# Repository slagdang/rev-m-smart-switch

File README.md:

# Smart switched outlet (2025) teardown

## History and product overview

A smart switched outlet is actually a device that plugs into a non-switched
outlet and has its own power outlet on it. The device is controllable remotely
over Wi-Fi and allows the device to be turned on and off.

This smart switched outlet is sold by Meross.
Meross describes it as a Matter smart plug.
It uses Matter over IPv6 over WiFi. It does not use Thread.
This is for US voltage and outlets. It was purchased in July 2025.
The device allows switching of the outlet and remote monitoring of
the switch state. It also allows continuous monitoring of the power
and energy usage by the attached switched device.

## Electrical background

In the US most appliances use 3-prong plugs with two parallel blade conductors
for the power conduction and a round pin for the protective ground.
The standard outlet for 120V at up to 15A (60Hz) is a NEMA 5-15R.
The plug that goes into it is a NEMA 5-15P.
The power is provided with one blade conductor that is at 120VAC RMS potential
compared to ground (called live, line or hot) and one blade conductor that
is at zero potential compared to ground (called neutral or return).

Protective ground should never be interrupted so that the device is grounded even
when off.
To turn a device off it is only necessary to interrupt the power circuit at any
point. This will cease current flow.
However it is safer to do this by interrupting the live conductor. This means all
circuitry in attached appliance will be at 0V potential as both conductors
still connected are at 0V potential.
To ensure the live is switched requires a polarized plug. In the US this is
done on ungrounded plugs with two different sized blades, one too large to fit
in the live slot. Grounded plugs with the round pin are inherently oriented
and do not require two different-sized blades.

## How it works

This device directly connects ground from the device socket to the wall plug
at all times. It also connects neutral continuously but places a current
sensing resistor in the path of the neutral connection.
It accomplishes its switching by interrupting the live line using a relay.

The relay is controlled using a single bit from a controller board that drives
a GPO line high or low. The main board also has an LED to indicate status
which is controlled by two GPO lines. It has a power and energy monitoring
chip which is read out by the controller board over a 4800bps 5V logic-level
RS-232 serial line.

## Circuit analysis

[view schematic as a PDF here.](smart-outlet-m-reverse.pdf)

The device contains a transformerless switching power supply to generate a
neutral-referenced 5V supply used to actuate the relay.
It has a 3.3V low dropout linear regulator to further reduce this for
use by the measurement chip and the microcontroller.
It contains a controller sub-module which has a Realtek Bluetooth radio
and microcontroller (RTL8720CM) which utilizes the 3.3V supply.
It measures current as a voltage differential across a 1mΩ sense resistor in
the neutral path from the device to the wall supply to measure instantaneous
current draw of the attached device.
It has a resistor chain from the live side into a voltage divider which is
then measured to determine the line voltage so power can be calculated.
It uses a 277V/16A-rated relay on the live side to turn the connected device
on and off.

The board has a bit over 1mm of creepage between RECT_AC and NEUTRAL_SRC.
It has the same clearance between the unswitched live and switched live.
For these conductors it is improved by using a 1mm slot.
The protective ground pin is not connected to anything inside except the
output receptacle.
The controller uses a GPO to turn the relay on and off through an NPN transistor.
It uses two GPOs to directly turn the LED red, green or off.
The controller uses a negative temperature coefficient thermistor to measure
the internal temperature of the device through an analog input,
presumably for protection.
The controller reads power draw parameters from a measurement chip over a
serial link.
The power input is fused for the controlling circuitry with a self-resetting
polyfuse and uses a metal-oxide varistor to withstand surges.
Power through the unit to the attached device is not protected with a fuse
or similar.

### Main schematic page

The function button (SW1) is read on a GPI to the controller board.
The button has an external pull up resistor (R23) so the GPI reads
high when the button is not pressed and low while it is pressed.

NTC1 is a temperature-sensitive resistor. It is read by being placed in a
resistive divider with R8. The node between them will change in voltage as
NTC1’s value changes. This voltage is read as an analog value through R7.
R7 will limit the current into the controller. As the analog input is
high impedance R7 does not form another voltage divider and so does not alter
the voltage read to a significant amount. The NTC1 cannot fully be
identified but likely has a B25/50 value of 4250K as this is the type
commonly used to measure human-scale ambient temperatures.

LED1 is referenced to 3.3V and so the emitters are turned on by driving
LED_RED or LED_GREEN low.

C13 and C14 are smoothing capacitors to smooth the voltage provided to the
controller circuitry.

### Power control page

Several functions are provided on this page. The simplest is to connect input
ground directly to the ground on the power outlet side.

The second is to
connect input neutral to the neutral on the power outlet side. Neutral
passes through a 1mΩ resistor, R10. This allows current
to be measured by measuring the voltage drop (differential voltage) across
R10. Differential voltage is measured using Kelvin (4-wire) sensing through
the nets NEUTRAL_SRC_SENSE and NEUTRAL_LOAD_SENSE. The voltage is measured
on the inside edge of each end endcap of the resistor using a parallel
path to the current path and the difference between the two will be 1mV
for each 1A of current drawn by the switched device.

The third function is to supply AC power to the power supply circuit so it
can create 5V DC power from the AC power. The line voltage is divided by a
resistive divider comprising R25 and VR1. Despite the differing reference
designators both R25 and VR1 are variable resistance devices. R25 is a PTC
(positive temperature coefficient) polyfuse. VR1 is an NTC (negative
temperature coefficient) metal oxide varistor (MOV). When
connected to the wall
R25 will have a low resistance (20Ω or so) and NTC1 will have a very high
resistance. So FUSED_AC will be the same as the line voltage. R25 will limit
inrush current. If the control circuity draws too much current on FUSED_AC
the current through R25 will cause R25 to increase its resistance greatly
("blow"). The polyfuse will reset after a period of time and things
will start again. This will
repeat until the fault is cleared or the polyfuse fails completely and
the unit ceases to operate. If there is a high voltage surge from the wall
source then VR1 will begin to conduct (around 775V) and this will change
the voltage divider so FUSED_AC is reduced in voltage. It also will
increase current draw through R25 and so likely will trigger the polyfuse
also.

The final function is to switch the output live power on and off
using a relay. Relay K1 connects the output live to the wall source when
energized. K1 is energized by the controller applying a positive
logic-level voltage on POWER_EN. Once the base (pin 1) of Q1 is 0.6V
or more positive than the emitter (pin 2) then current flows into
the collector (pin 3) and out the emitter. This happens when POWER_EN
is driven high by the controller. This induces a current through R22
and the base. The current will be at least 3mA. This will cause Q1 to
attempt to drive at least 117mA through the collector through the coil
of K1. This is more
than enough to energize K1 fully. D4 serves to snub the voltage the
inductor (coil) in K1 produces momentarily when Q1 is switched off.
C17 serves to reduce the draw on +5V when the coil is first switched
on by producing a low ESR charge store.

### Power supplies page

The top half of this is a sophisticated neutral-referenced transformerless
switch-mode power supply (SMPS). The sophistication is mostly contained
within U1 and will not be fully explained here.

The short version is that U1 takes unregulated energy in and outputs
a reduced regulated voltage. It is capable of converting excess
voltage into increased current similar to how a transformer does
and the power (Watts) in is similar to the power out, just the
available voltage at the output is lower than the input and the
available current is increased inversely. It does this by rapidly
switching its output on and off to send energy into an inductor.
This inductor stores the energy in its magnetic field. It is drawn
off by the devices being supplied. It adjusts its switching duty
cycle so as to send the right amount of energy into the inductor
to match the energy being drawn out of the inductor and thus
keep the inductor voltage relatively constant. The inductor’s
resistance to current change and its ability to store energy in
its magnetic field are critical in making this happen.

Fused AC power at about 120V RMS comes in on FUSED_AC. D2 performs a positive
half-wave rectification on the AC. D5 applies a redundant half-wave
rectification. D5 is present only because diodes have some tendency to
become short circuits when failing. This would put AC voltage into the
circuit and produce a small conflagration within the device. By having two
diodes both D2 and D5 have to fail short to produce this result. This
should reduce the incidence of these small fires to the square of the
incidence rate with a single diode. So if this failure rate would be
one in one thousand over the life of the product then with two
consecutive diodes the failure rate would drop to one in a million
instead.

U1 and L2 work in tandem to drive the right-hand side of L2 to the
regulated voltage. This puts 5V across C7. R9 provides a minimum
current draw at the output to make the result of regulation through
switching more accurate.
U1 is rated for up to 300mA output current.

The bottom half of this page is a low-dropout linear regulator. A
linear regulator works by "burning off" any excess voltage at
the input so that the output voltage is regulated to the desired
value. This is usually done internally with a load resistor,
a current shunt and an op-amp.
U3 provides this regulation functionality on its own
and is fixed at 3.3V target output voltage. C10 and C11 provide
output smoothing. C9 provides input smoothing and
increases ripple rejection.

### Current measurement page

U3 is a complete current, voltage and power measurement solution.
It provides instantaneous voltage, current and power measurements
over a 4800bps 5V logic-level RS-232 serial link repeatedly every
54.912ms. These measurements can be accumulated over time to
calculate total energy used. The resistive divider created by
R12 and R13 reduce the serial output signal to 3.3V as the
controller uses 3.3V I/O. C15 provides supply voltage smoothing to
U3.

U3 measures the input voltage on pin 4 (V2P). Pin 4 cannot be
outside the range ±2V relative to GND. To overcome this the
resistive divider created by R14, R15, R16, R17 and R18 reduces
the input voltage to 0.0532% of the input voltage. This puts the
voltage in the range of ±100mV. Using multiple resistors is common
because of the high value needed and the high voltage at the
top of the divider. With 4 resistors on top of the ladder
each only drops up to 40V and so operates within the voltage
rating of an 0805 resistor instead of having to use a
more expensive large
format resistor. C16 smoothes the voltage and also
resists droop of the voltage when the sample and hold capacitor
on pin 4 captures the signal.

U3 measures the input current on pins 2 and 3 (V1P, V1N).
NEUTRAL_LOAD_SENSE and NEUTRAL_SRC_SENSE are connected to the
current sense resistor using the inner edges of the pads so
as to create a parallel path for voltage sensing (4-wire sensing).
R20, R24, C18 and C19 create low pass filters to reduce
unrepresentative readings for loads with spiky current draws.
Pins 2 and 3 are both on the neutral line which is no more than
1mΩ from GND and so should not
produce voltages which differ more than ±100mV from GND.

## Meta-analysis

Any criticisms here are constructive and do not necessarily indicate a serious
flaw in the product.

The power supply chip employed suggests using a full-bridge rectifier for its AC input.
However this design uses half-wave. It does however put two diodes in series so that
a single diode failing short does not produce a short. This is probably a reasonable
design choice.

The power supply chip regulates voltage referenced to system ground but is not
connected to system ground. Regulation is surely still acceptable but likely
less precise than could be achieved with a direct connection to the ground
reference.

The device contains no X-class capacitor at all. One is suggested for the power
supply chip but it is omitted. With no non-resetting fuse inside this may be the
right choice. It does seem to go against the company claims of "protection against
short-circuits" somewhat. Even if this has some software in the controller to
turn off on a measured overcurrent or over-temperature this device is relying on
wall circuit protection for true overcurrent protection.

While the device has internal temperature monitoring of a sort due to NTC1
it has no failsafe method of using that to prevent overheat. If the failure
which produces the overheat is not in the controller itself then the controller
will presumably use the temperature readings to shut down the attached device.
If the control circuity itself fails it will hopefully be shut down by the polyfuse
due to overcurrent.

The wireless interface chip is rated by the manufacturer at 500mA max current
draw. It is powered by a 3.3V LDO which is in a package too small to be rated
at 500mA. It surely is rated at 300mA or less. Despite this the LDO has 20µF of
capacitance on the outputvside. This normally would be for a 2A regulator.
In this case it seems that these capacitors are sized to try to make enough
instantaneous current available to overcome
the underrating of the LDO for short periods of high draw.
This seems to work fine but no measurements were made.

Measurements in U3 may be scaled up or down by choices of different
current sense resistors and voltage dividers. This must be
compensated for in software on the controller or on device software
that receives the readings over the network as U3 does not receive
commands and so cannot be instructed to rescale its calculations.

The small slit around the single button is not gasketed unlike another smart switched
outlet I purchased. This would mean liquids could ingress. It is nearest a low voltage
portion of the board and of course the button. The device also has the
receptacle on the front and those are not sealed so water could ingress there also
as it could on any similar device.

There are small quirks about the board layout. Unnecessary vias, etc. It uses a lot
of small floods in places. None of these issues are of importance.

### teardown images

### Device identification

The device is approximately 70mm wide by 40mm high by 40mm deep.
It has a NEMA 5-15P on the back to plug into a US outlet. It has
a NEMA 5-15R on the front for plugging in the device you wish to switch.
It is rated for 15 amps in and out and "120V" (presumably RMS nominal).

On the back it is identified as:

Smart WiFi Plug Mini

Model: MSS315

It lists as containing FCC ID 2AMUU-MWA05 and IC 24963-MWA06

## Design tools

This is a KiCAD 9.X project. KiCAD is a free electronic design tool
[available at kicad.org](https://kicad.org/).

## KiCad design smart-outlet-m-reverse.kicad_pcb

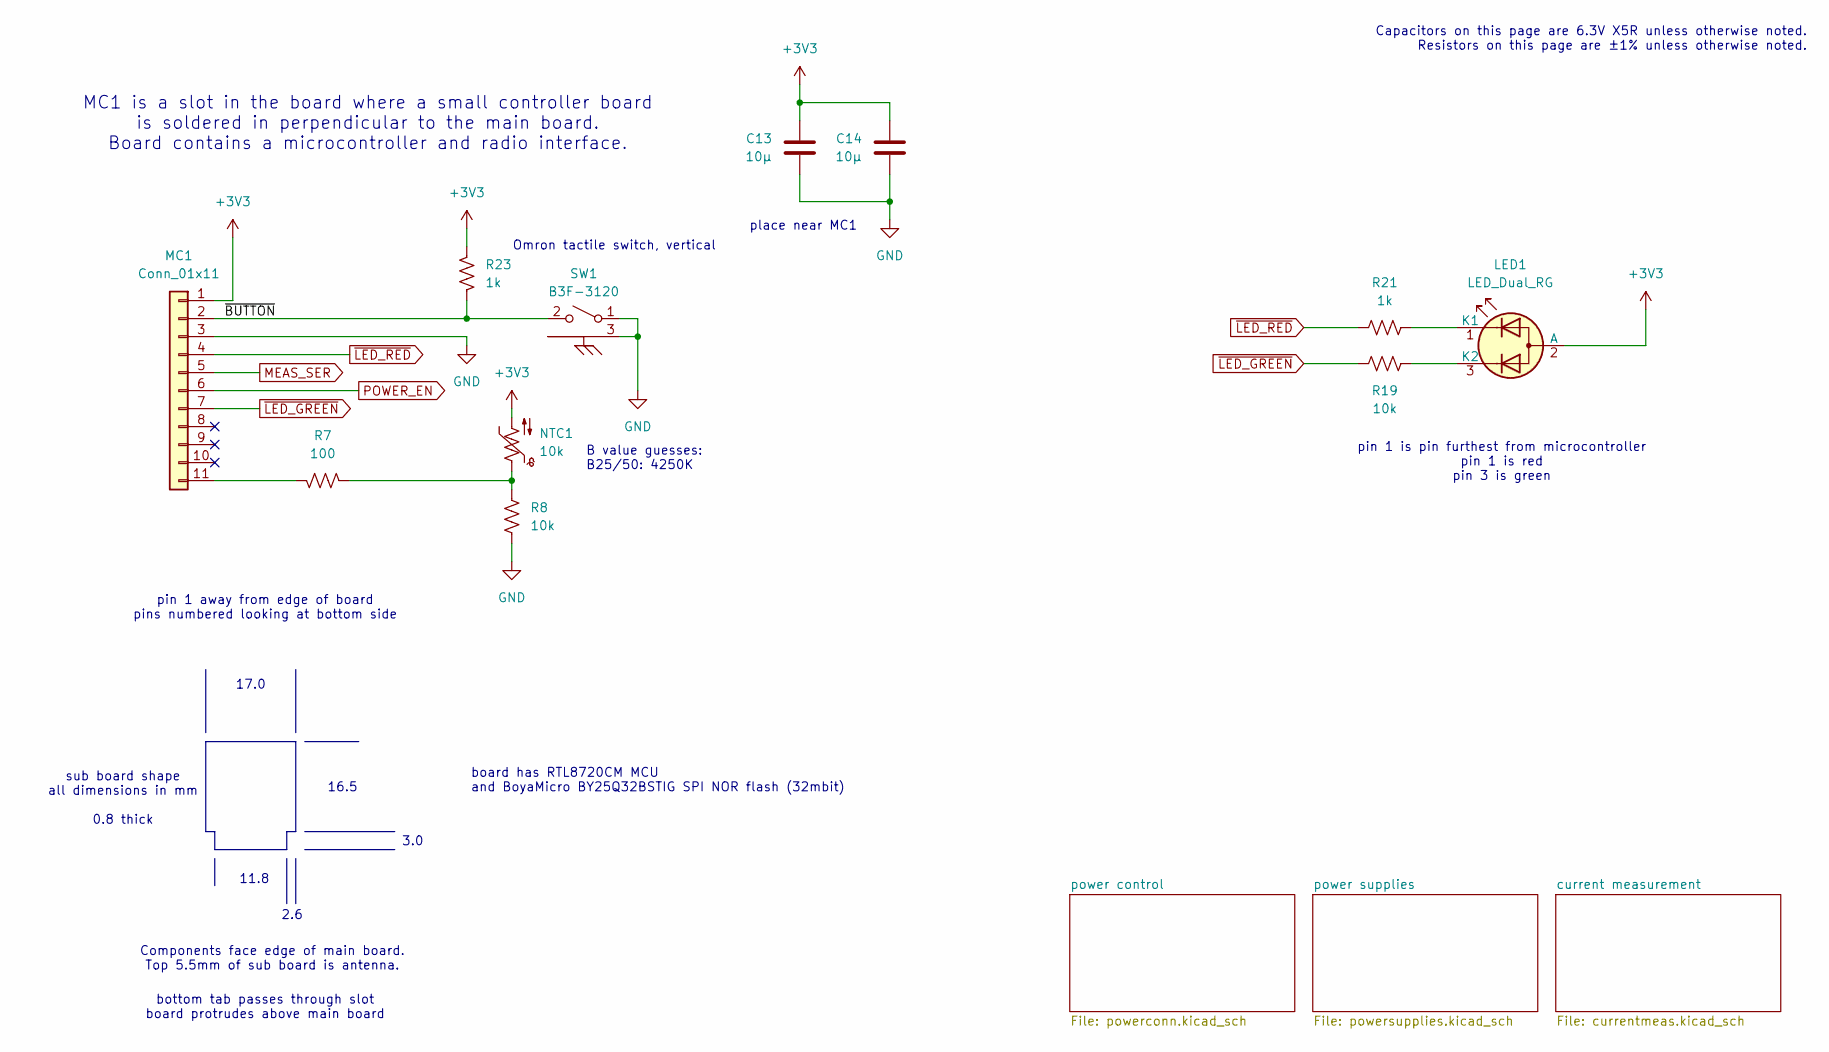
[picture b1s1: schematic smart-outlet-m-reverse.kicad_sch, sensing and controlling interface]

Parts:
C13, C14: 10µ; C_0402_1005Metric
LED1: LED_Dual_RG; LED_D3.0mm-3_Horiz
MC1: Conn_01x11; BoardToBoardInterface_11xP1.00mm
NTC1: 10k; R_0402_1005Metric
R7: 100; R_0402_1005Metric
R8, R19: 10k; R_0402_1005Metric
R21, R23: 1k; R_0402_1005Metric
SW1: B3F-3120; SW_SPST_Omron_B3F-315x_Angled

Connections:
+3V3: C13.2, C14.2, LED1.2 (A), MC1.1, NTC1.2, R23.1; also elsewhere on the board
/~BUTTON: MC1.2, R23.2, SW1.2 (B)
MEAS_SER: MC1.5; also elsewhere on the board
NEUTRAL_SRC: C13.1, C14.1, MC1.3, R8.1, SW1.1 (A), SW1.3; also elsewhere on the board
unnamed: LED1.1 (K1), R21.2
unnamed: LED1.3 (K2), R19.2
unnamed: MC1.11, R7.1
unnamed: NTC1.1, R7.2, R8.2
POWER_EN: MC1.6; also elsewhere on the board
~LED_GREEN: MC1.7, R19.1
~LED_RED: MC1.4, R21.1

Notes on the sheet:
2.6
bottom tab passes through slot board protrudes above main board
11.8
Omron tactile switch, vertical
3.0
16.5
place near MC1
B value guesses: B25/50: 4250K
sub board shape all dimensions in mm 0.8 thick
pin 1 away from edge of board pins numbered looking at bottom side
17.0
pin 1 is pin furthest from microcontroller pin 1 is red pin 3 is green
MC1 is a slot in the board where a small controller board is soldered in perpendicular to the main board. Board contains a microcontroller and radio interface.
board has RTL8720CM MCU and BoyaMicro BY25Q32BSTIG SPI NOR flash (32mbit)
Capacitors on this page are 6.3V X5R unless otherwise noted. Resistors on this page are ±1% unless otherwise noted.
Components face edge of main board. Top 5.5mm of sub board is antenna.

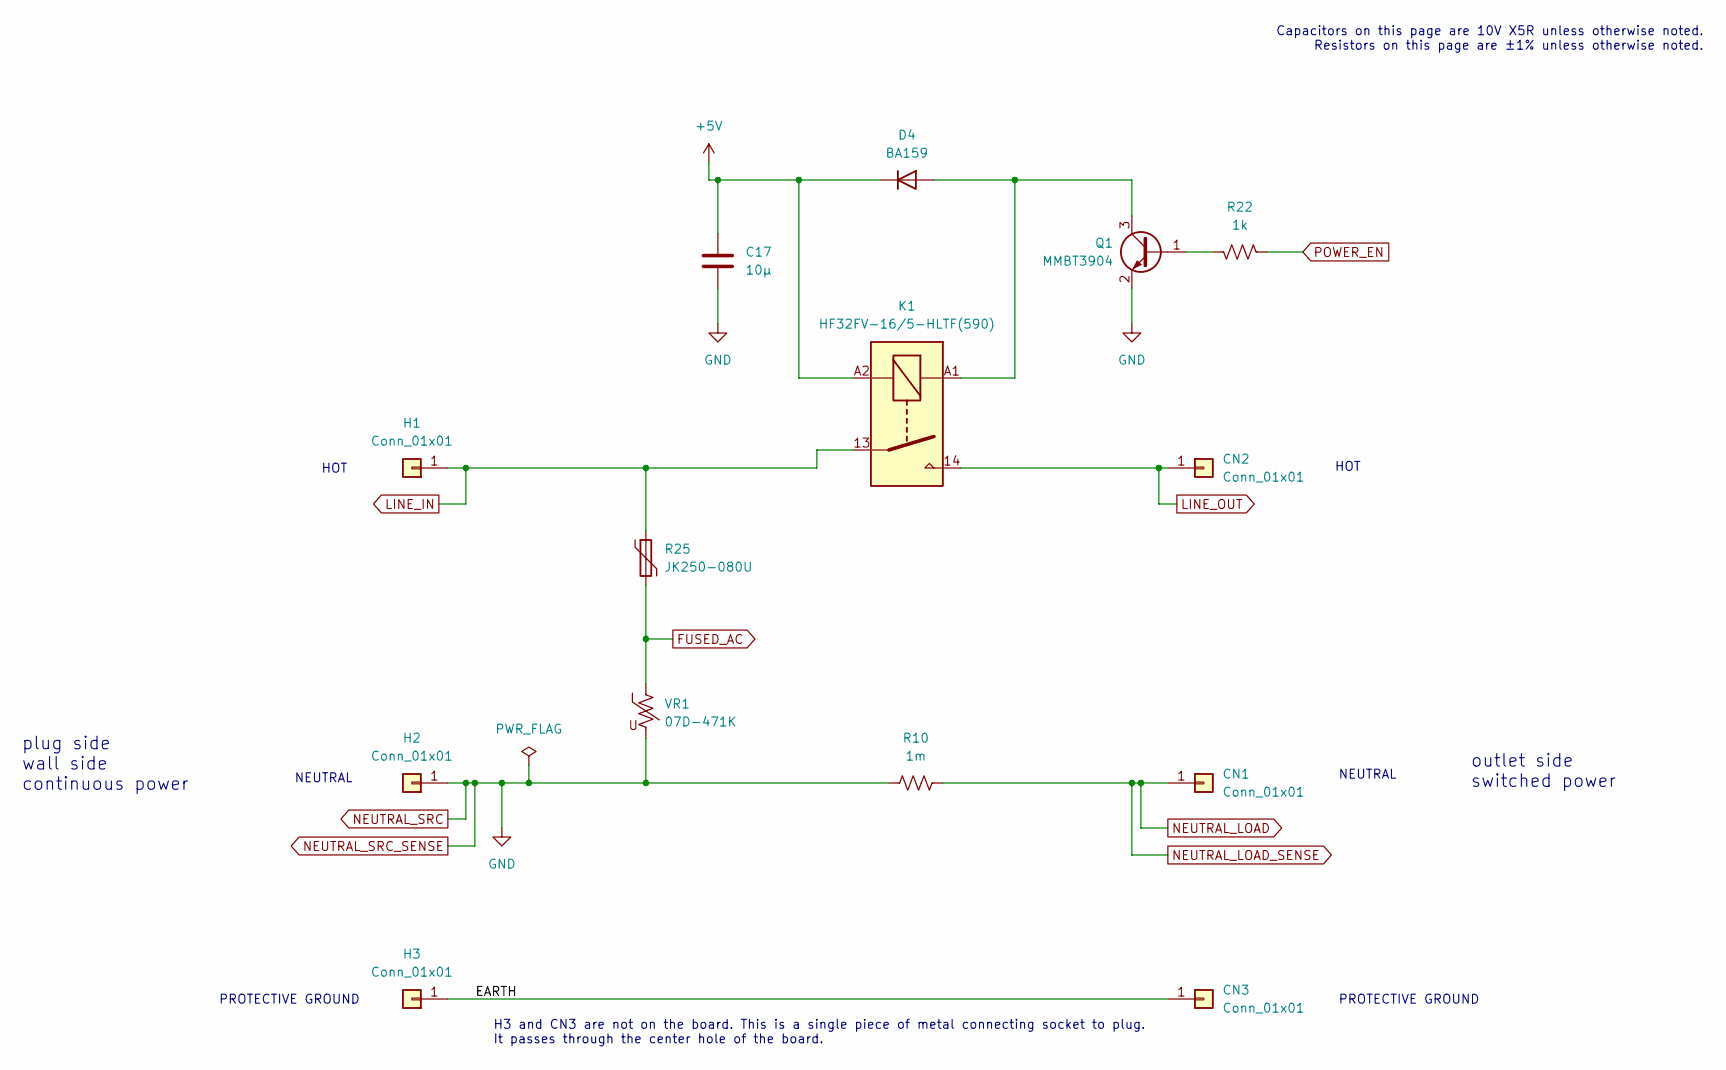
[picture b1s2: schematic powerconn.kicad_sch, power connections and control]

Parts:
C17: 10µ; C_0603_1608Metric
CN1, CN2: Conn_01x01; NEMA5R_blade
CN3: Conn_01x01; PinHeader_1x01_P2.54mm_Vertical
D4: BA159; D_SOD-123F
H1, H2: Conn_01x01; NEMA5P_post
H3: Conn_01x01; PinHeader_1x01_P2.54mm_Vertical
K1: HF32FV-16/5-HLTF(590); HF_Relay_subminature_A_THT_18.4x10.2mm
Q1: MMBT3904; SOT-23
R10: 1m; R_2512_6332Metric
R22: 1k; R_0402_1005Metric
R25: JK250-080U; Fuse_Littelfuse_395Series
VR1: 07D-471K; RV_Disc_D9mm_W6.1mm_P5mm

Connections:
+5V: C17.1, D4.1 (K), K1.A2; also elsewhere on the board
FUSED_AC: R25.2, VR1.1; also elsewhere on the board
LINE_IN: H1.1, K1.13, R25.1
LINE_OUT: CN2.1, K1.14
NEUTRAL_LOAD: CN1.1, R10.2; also elsewhere on the board
NEUTRAL_SRC: C17.2, H2.1, Q1.2 (E), R10.1, VR1.2; also elsewhere on the board
unnamed: CN3.1, H3.1
unnamed: D4.2 (A), K1.A1, Q1.3 (C)
unnamed: Q1.1 (B), R22.2
POWER_EN: R22.1; also elsewhere on the board

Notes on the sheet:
Capacitors on this page are 10V X5R unless otherwise noted. Resistors on this page are ±1% unless otherwise noted.
PROTECTIVE GROUND
HOT
plug side wall side continuous power
outlet side switched power
NEUTRAL
H3 and CN3 are not on the board. This is a single piece of metal connecting socket to plug. It passes through the center hole of the board.

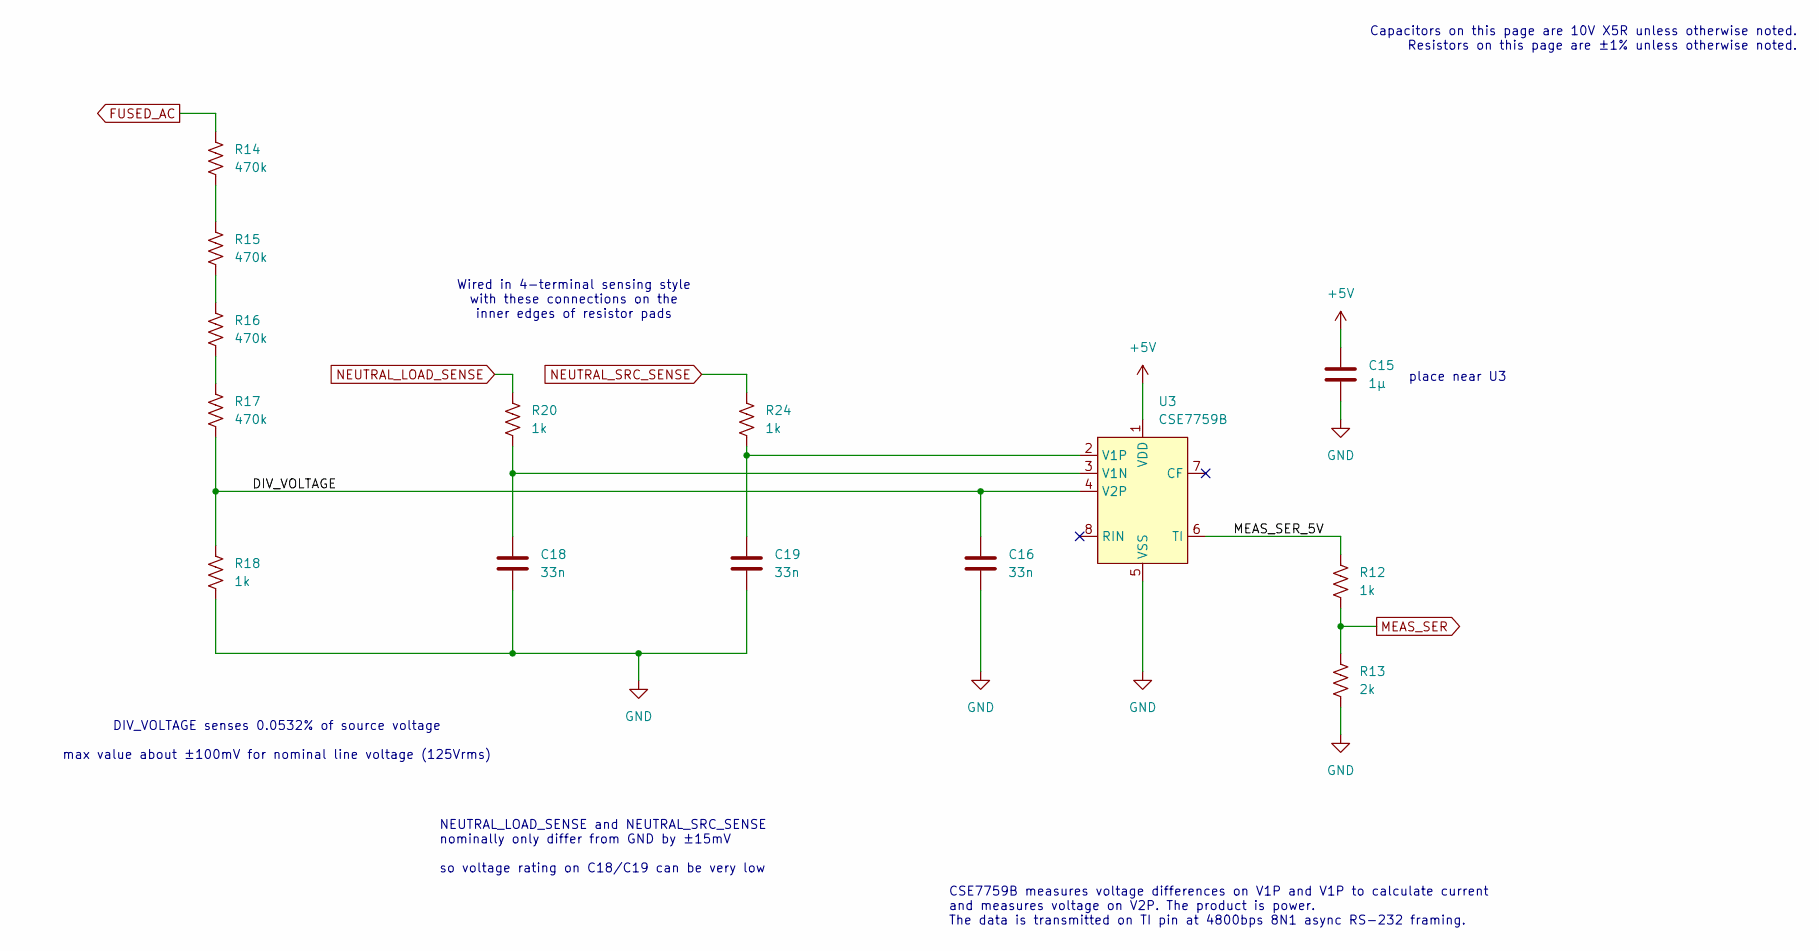
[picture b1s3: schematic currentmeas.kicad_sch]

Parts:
C15: 1µ; C_0402_1005Metric
C16, C18, C19: 33n; C_0402_1005Metric
R12, R18, R20, R24: 1k; R_0402_1005Metric
R13: 2k; R_0402_1005Metric
R14, R15, R16, R17: 470k; R_0805_2012Metric
U3: CSE7759B; SO-8_3.9x4.9mm_P1.27mm

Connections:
+5V: C15.1, U3.1 (VDD); also elsewhere on the board
/current measurement/DIV_VOLTAGE: C16.1, R17.1, R18.2, U3.4 (V2P)
/current measurement/MEAS_SER_5V: R12.1, U3.6 (TI)
FUSED_AC: R14.2; also elsewhere on the board
MEAS_SER: R12.2, R13.1; also elsewhere on the board
NEUTRAL_LOAD: R20.1; also elsewhere on the board
NEUTRAL_SRC: C15.2, C16.2, C18.2, C19.2, R13.2, R18.1, R24.1, U3.5 (VSS); also elsewhere on the board
unnamed: R14.1, R15.2
unnamed: R15.1, R16.2
unnamed: R16.1, R17.2
unnamed: C18.1, R20.2, U3.3 (V1N)
unnamed: C19.1, R24.2, U3.2 (V1P)

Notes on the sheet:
NEUTRAL_LOAD_SENSE and NEUTRAL_SRC_SENSE nominally only differ from GND by ±15mV so voltage rating on C18/C19 can be very low
Capacitors on this page are 10V X5R unless otherwise noted. Resistors on this page are ±1% unless otherwise noted.
place near U3
Wired in 4-terminal sensing style with these connections on the inner edges of resistor pads
CSE7759B measures voltage differences on V1P and V1P to calculate current and measures voltage on V2P. The product is power. The data is transmitted on TI pin at 4800bps 8N1 async RS-232 framing.
DIV_VOLTAGE senses 0.0532% of source voltage max value about ±100mV for nominal line voltage (125Vrms)

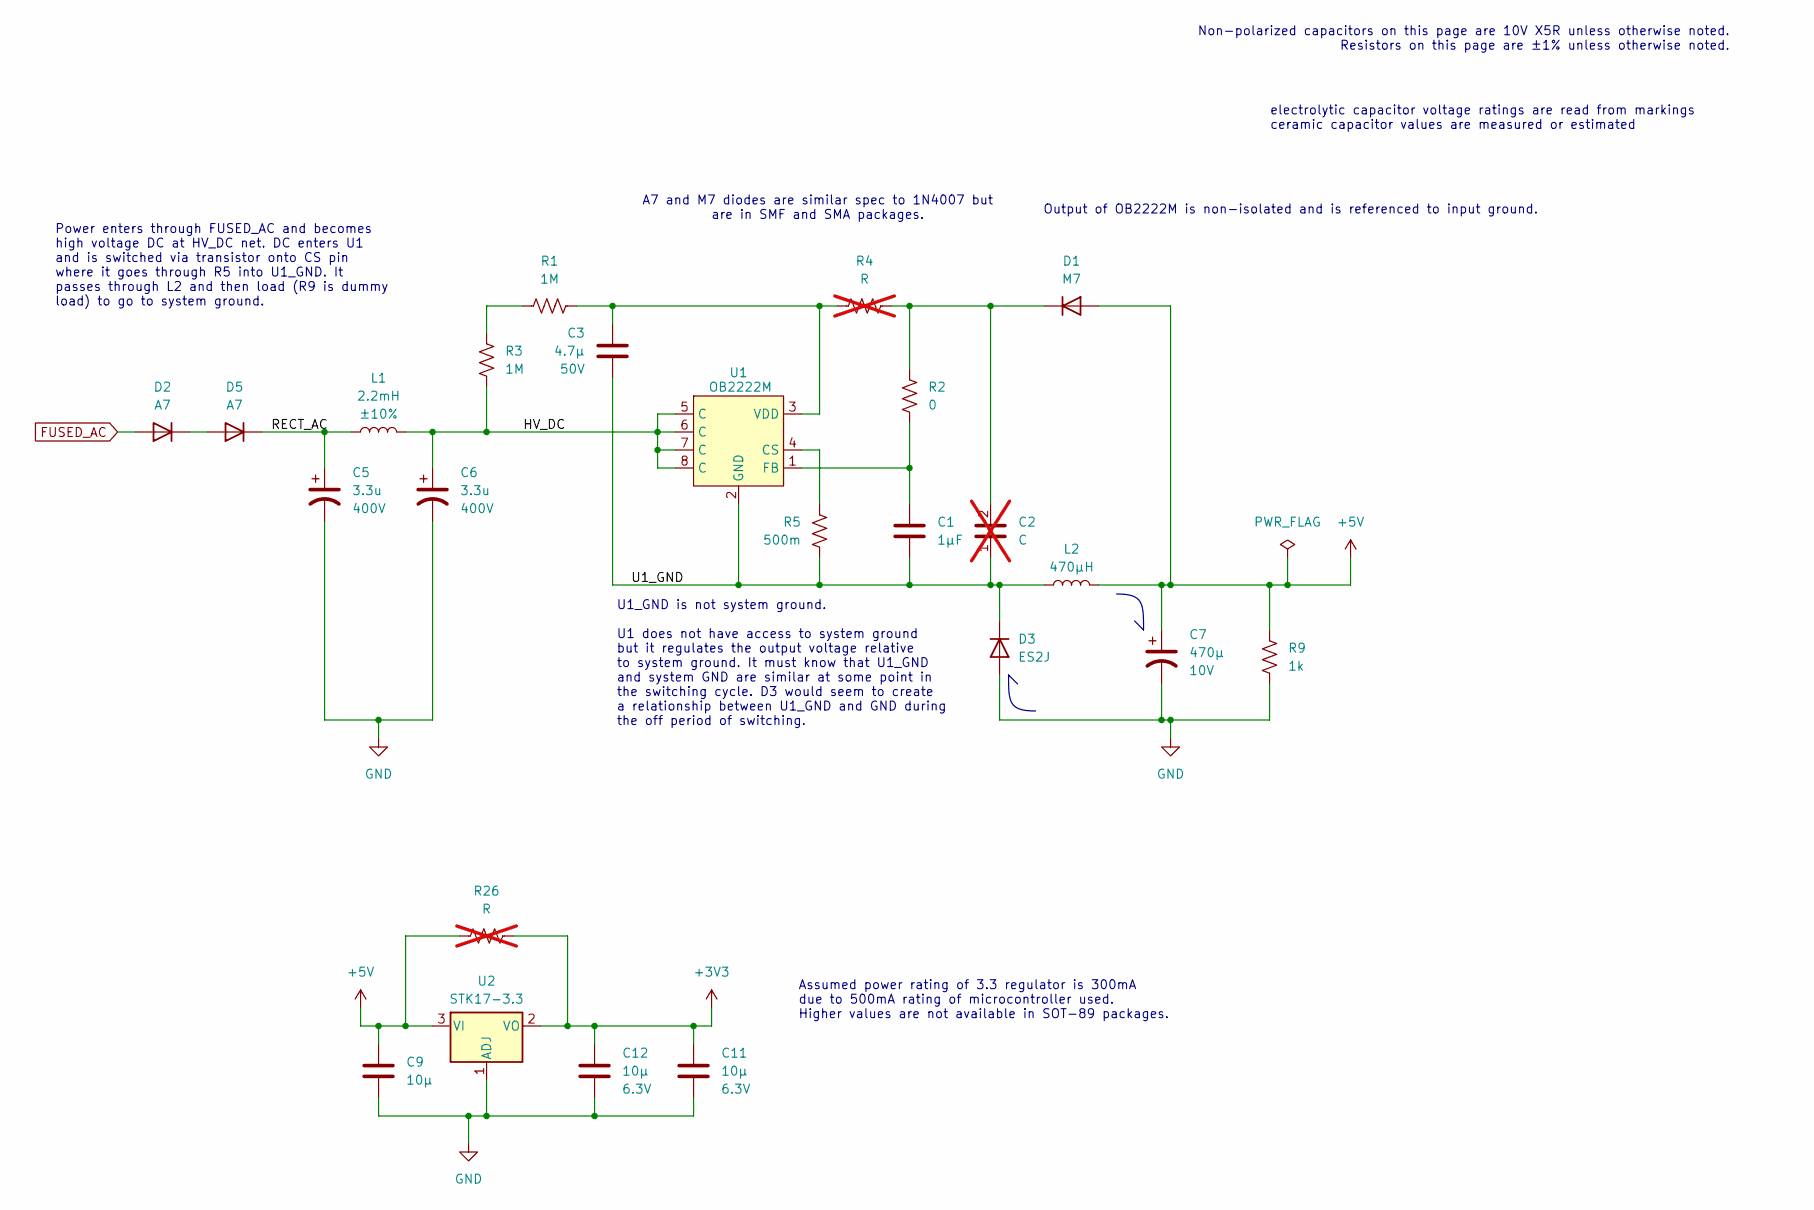
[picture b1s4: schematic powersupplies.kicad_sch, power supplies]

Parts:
C1: 1µF; C_0603_1608Metric
C2: C; C_0603_1608Metric; not fitted
C3: 4.7µ; C_0805_2012Metric; Voltage 50V
C5, C6: 3.3u; CP_Radial_D6.3mm_P2.50mm; Voltage 400V
C7: 470µ; CP_Radial_D6.3mm_P2.50mm; Voltage 10V
C9: 10µ; C_0603_1608Metric
C11, C12: 10µ; C_0402_1005Metric; Voltage 6.3V
D1: M7; D_SMA
D2, D5: A7; D_SOD-123F
D3: ES2J; D_SMA
L1: 2.2mH; L_Axial_L9.5mm_D4.0mm_P3.81mm_Vertical; Tolerance ±10%
L2: 470µH; L_Radial_D8.7mm_P5.00mm_Fastron_07HCP
R1, R3: 1M; R_0805_2012Metric
R2: 0; R_0603_1608Metric
R4, R26: R; R_0603_1608Metric; not fitted
R5: 500m; R_1206_3216Metric
R9: 1k; R_0603_1608Metric
U1: OB2222M; SO-8_3.9x4.9mm_P1.27mm
U2: STK17-3.3; SOT-89-3

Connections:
+3V3: C11.2, C12.2, R26.2, U2.2 (VO); also elsewhere on the board
+5V: C7.1, C9.2, D1.2 (A), L2.2, R9.1, R26.1, U2.3 (VI); also elsewhere on the board
/power supplies/HV_DC: C6.1, L1.2, R3.1, U1.5 (C), U1.6 (C), U1.7 (C), U1.8 (C)
/power supplies/RECT_AC: C5.1, D5.1 (K), L1.1
/power supplies/U1_GND: C1.2, C2.1, C3.2, D3.1 (K), L2.1, R5.2, U1.2 (GND)
FUSED_AC: D2.2 (A); also elsewhere on the board
NEUTRAL_SRC: C5.2, C6.2, C7.2, C9.1, C11.1, C12.1, D3.2 (A), R9.2, U2.1 (ADJ); also elsewhere on the board
unnamed: C2.2, D1.1 (K), R2.2, R4.2
unnamed: D2.1 (K), D5.2 (A)
unnamed: R1.2, R3.2
unnamed: R5.1, U1.4 (CS)
unnamed: C1.1, R2.1, U1.1 (FB)
unnamed: C3.1, R1.1, R4.1, U1.3 (VDD)

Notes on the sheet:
Output of OB2222M is non-isolated and is referenced to input ground.
Assumed power rating of 3.3 regulator is 300mA due to 500mA rating of microcontroller used. Higher values are not available in SOT-89 packages.
Power enters through FUSED_AC and becomes high voltage DC at HV_DC net. DC enters U1 and is switched via transistor onto CS pin where it goes through R5 into U1_GND. It passes through L2 and then load (R9 is dummy load) to go to system ground.
U1_GND is not system ground. U1 does not have access to system ground but it regulates the output voltage relative to system ground. It must know that U1_GND and system GND are similar at some point in the switching cycle. D3 would seem to create a relationship between U1_GND and GND during the off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
A7 and M7 diodes are similar spec to 1N4007 but are in SMF and SMA packages.
electrolytic capacitor voltage ratings are read from markings ceramic capacitor values are measured or estimated
Non-polarized capacitors on this page are 10V X5R unless otherwise noted. Resistors on this page are ±1% unless otherwise noted.

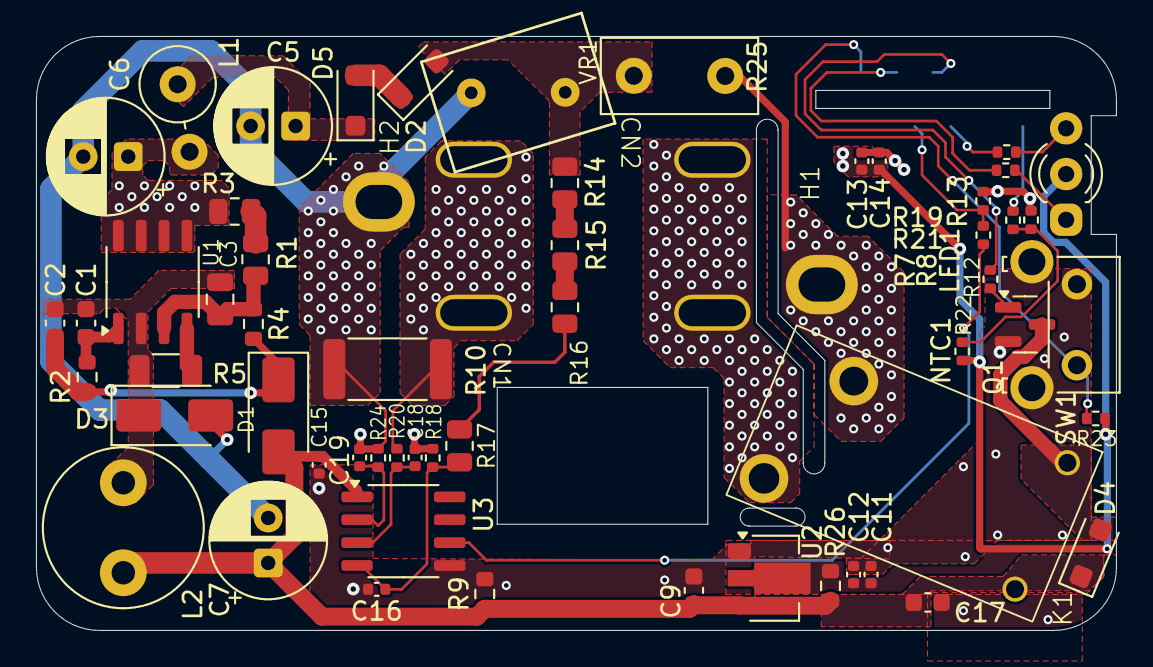
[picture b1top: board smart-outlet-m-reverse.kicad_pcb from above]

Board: 2 copper layers, 60.0 x 33.0 mm, 61 parts (1 on the bottom side), 34 nets.

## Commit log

2025-07-18 First version
2025-07-18 Cleaning up layout
2025-07-20 All parts on. Set foots for everything. Time to try a layout.
2025-07-21 Made a first board layout.
2025-07-25 Have a full board layout which resembles the original in some ways. Made a few schematic fixes to match better.
2025-07-26 Making board layout match better. Added new footprints and symbols.
2025-07-26 All values determined for schematic. From measurements, datasheets, or reading markings.
2025-07-29 Fixed plug and receptacle foots. No components left to fix but L1? And the silk and fab layers. And some kind of labeling of the design.
2025-07-29 Fixed silk, fixed fab. Fixed a few part 3D models. Starting to rename stuff.
2025-07-29 Renamed things. Removed reference image. Ready for the world.
2025-07-29 Added board notes.
2025-07-29 Added CC0 license.
2025-07-29 Added information on microcontroller sub-board.
2025-07-30 Create README.md
    Describes the project some.
2025-07-30 Despite so many vias I realized I hadn't added some where they matter. Corrected.
2025-08-18 Rearranged SMPS circuit. Added a lot of schematic comments. Moved RECT_AC line away from NEUTRAL_SRC (not enough). Updated README greatly. Added pictures. Added PDF schematic.
2025-08-18 Forgot to update schematic PDF.
